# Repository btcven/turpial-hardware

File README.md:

# Turpial Hardware

Source files for Turpial hardware, designed using KiCAD v5.

## License

Copyright (C) 2021 Locha Mesh Developers

Licensed under the OHL-W-v2 Open Hardware license.

See [LICENSE](./LICENSE) for more information.

## The PCB Stack

According to the recomendations of Texas Instruments the stack will be a 4 layers sandwitch containing:

### Layers, view and dimensions

### Vias, view and dimensions

## Plugins and Tools

### Required

#### RF Tools _KICAD PLUGIN_
    URL: https://github.com/easyw/RF-tools-KiCAD

####  Teardrops
    URL: https://github.com/NilujePerchut/kicad_scripts

### Optionals

#### INTERACTIVE BOM _KICAD PLUGIN_
    Description: Generate an interactive html Bill Of Materials (BOM)
    URL: https://github.com/openscopeproject/InteractiveHtmlBom
    
#### GRAPHICAL SYMBOL GENERATOR (KiSymGen) _KICAD PLUGIN_
    Description: KiSymGen is a graphical symbol generator which makes this process visual and less painful.
    URL: https://github.com/pixellon/imgui
    
#### library.io _ONLINE_TOOL_
    Description: Instantly generate PCB packages by entering a few dimensions from a data sheet.
    URL: https://library.io/

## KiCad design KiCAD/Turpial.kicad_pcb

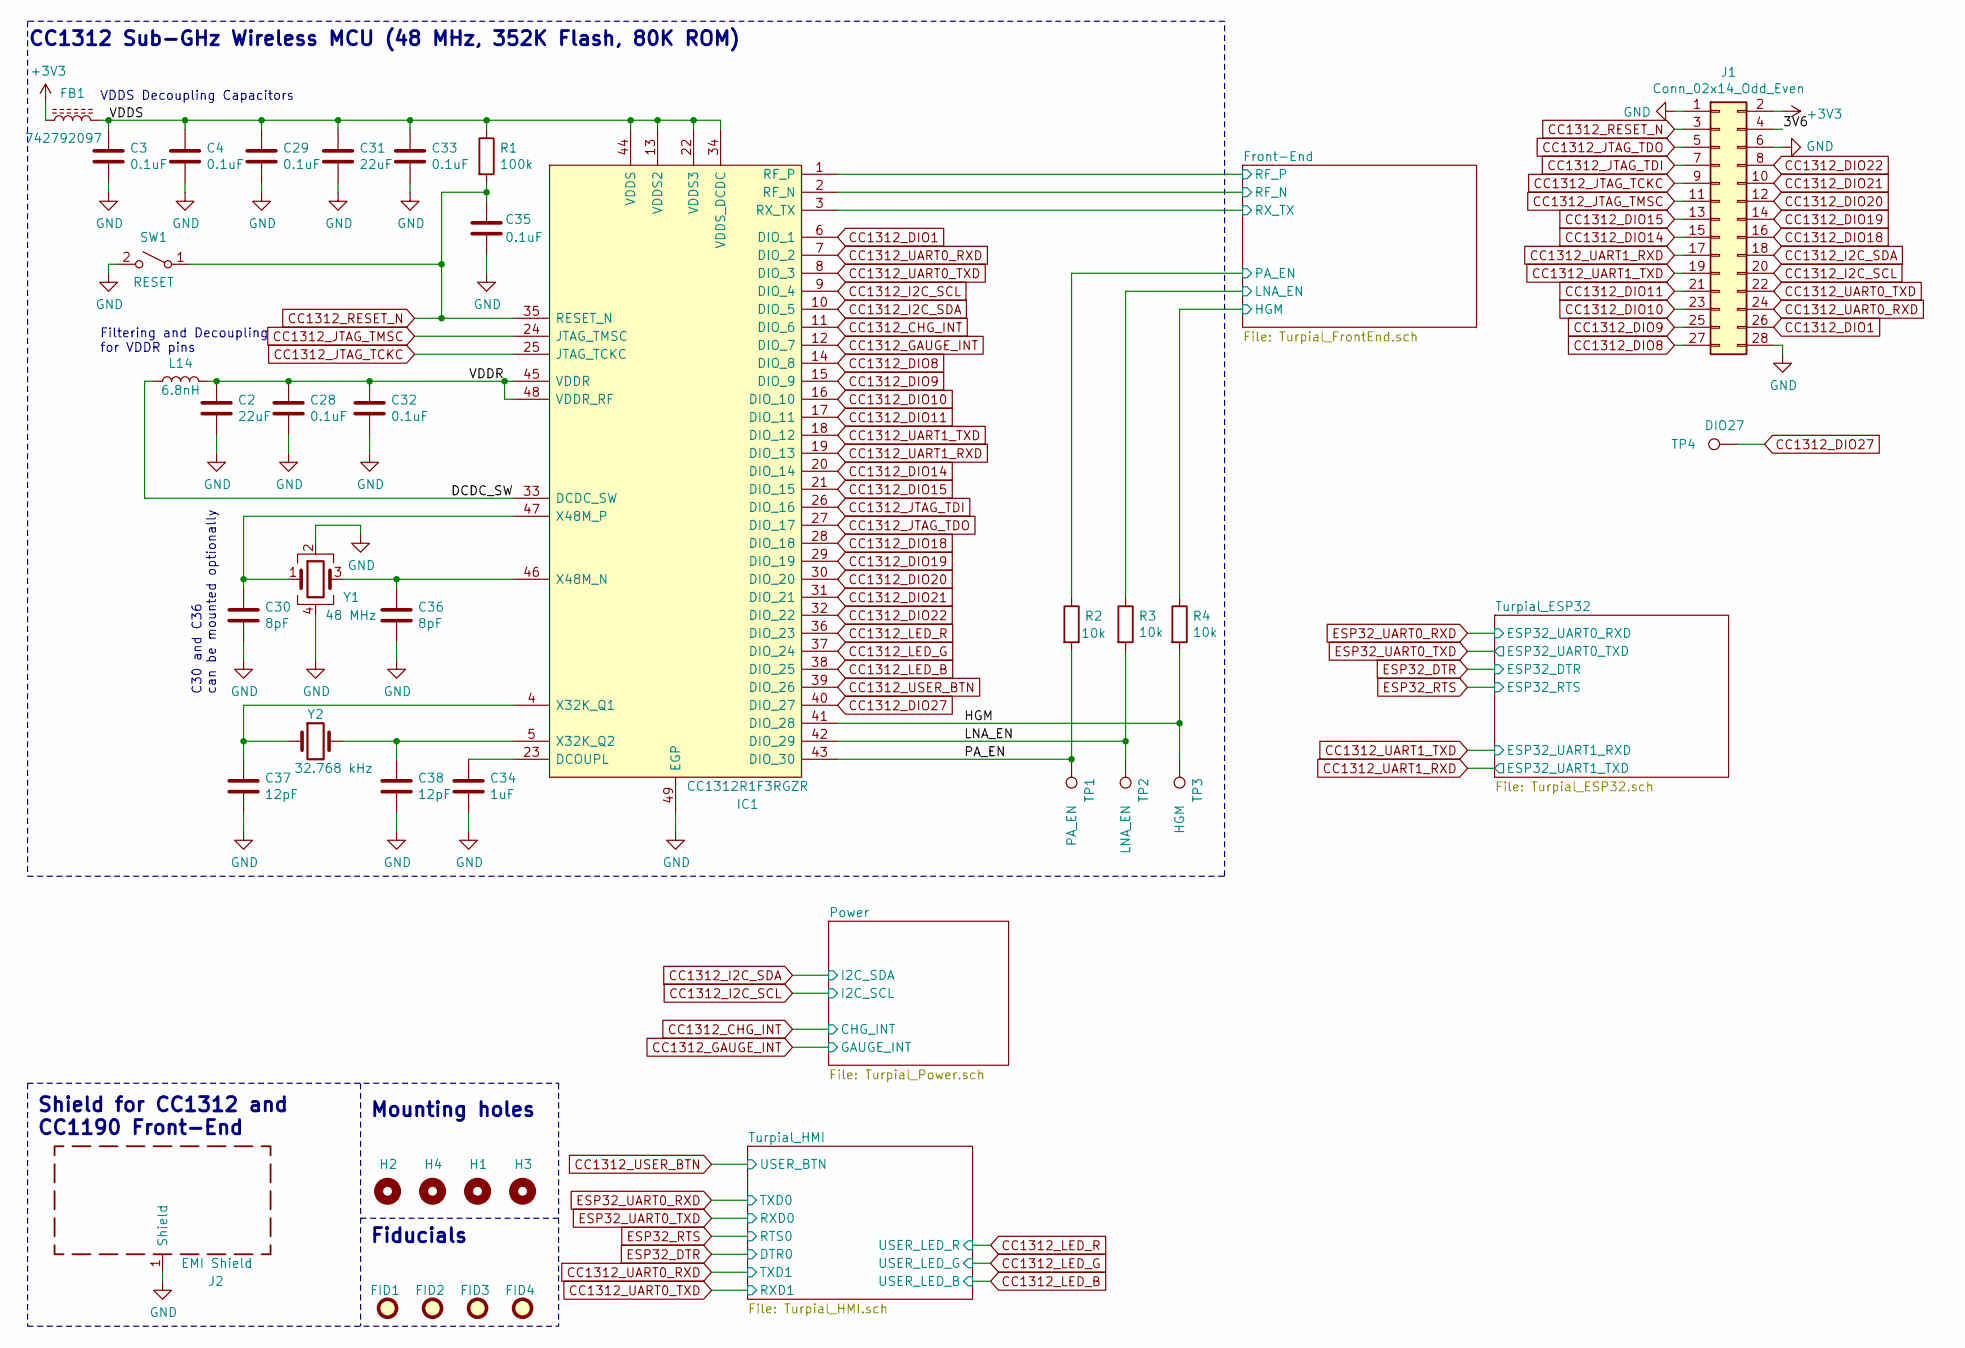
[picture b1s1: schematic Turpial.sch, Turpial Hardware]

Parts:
C2, C31: 22uF; C_0805_2012Metric; Manufacturer_Part_Number GRM21BR61E226ME44L; Mouser Part Number 81-GRM21BR61E226ME4L
C3, C4, C28, C29, C32, C33, C35: 0.1uF; C_0402_1005Metric; Manufacturer_Part_Number GRM155R61H104KE19D; Mouser Part Number 81-GRM155R61H104KE9D
C30, C36: 8pF; C_0402_1005Metric; Manufacturer_Part_Number GRM0225C1E8R0WA03L; Mouser Part Number 81-GRM0225C1E8R0WA3L
C34: 1uF; C_0402_1005Metric; Manufacturer_Part_Number GRM155R61E105KA12D; Mouser Part Number 81-GRM155R61E105KA2D
C37, C38: 12pF; C_0402_1005Metric; Manufacturer_Part_Number GJM1555C1H120JB01D; Mouser Part Number 81-GJM1555C1H120JB1D
FB1: 742792097; L_0805_2012Metric; Manufacturer_Part_Number 742792097; Mouser Part Number 710-742792097
FID1, FID2, FID3, FID4: Fiducial; Fiducial_1mm_Mask2mm
H1, H2, H3, H4: MountingHole; MountingHole_2.5mm_Pad_Via
IC1: CC1312R1F3RGZR; Texas_S-PVQFN-N48_EP5.15x5.15mm_ThermalVias; Manufacturer_Part_Number CC1312R1F3RGZR; Mouser Part Number 595-CC1312R1F3RGZR
J1: Conn_02x14_Odd_Even; PinHeader_2x14_P2.54mm_Vertical_SMD; Manufacturer_Part_Number 15-91-2140; Mouser Part Number 538-15-91-2140
J2: EMI Shield; SMS-461-F; Manufacturer_Part_Number SMS-461F; Mouser Part Number 861-SMS-461F
L14: 6.8nH; L_0805_2012Metric; Manufacturer_Part_Number MLZ2012N6R8LT000; Mouser Part Number 810-MLZ2012N6R8LT000
R1: 100k; R_0402_1005Metric; Manufacturer_Part_Number RC0402FR-7D100KL; Mouser Part Number 603-RC0402FR-7D100KL
R2, R3, R4: 10k; R_0402_1005Metric; Manufacturer_Part_Number RC0402FR-0710KL; Mouser Part Number 603-RC0402FR-0710KL
SW1: RESET; WS-TASU-Series
TP1: PA_EN; TestPoint_Pad_D1.0mm
TP2: LNA_EN; TestPoint_Pad_D1.0mm
TP3: HGM; TestPoint_Pad_D1.0mm
TP4: DIO27; TestPoint_Pad_D1.0mm
Y1: 48 MHz; Crystal_SMD_2016-4Pin_2.0x1.6mm; Manufacturer_Part_Number NX2016SA-48M-EXS00A-CS08718; Mouser Part Number 344-NX2016SA48S08718
Y2: 32.768 kHz; Crystal_SMD_3215-2Pin_3.2x1.5mm; Manufacturer_Part_Number FC-135 32.7680KA-A3; Mouser Part Number 732-FC135-32.76KAA3

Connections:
+3V3: FB1.1, J1.2; also elsewhere on the board
/3V6: J1.4
/DCDC_SW: IC1.33 (DCDC_SW), L14.1
/Front-End/HGM: R4.1; also elsewhere on the board
/Front-End/LNA_EN: R3.1; also elsewhere on the board
/Front-End/PA_EN: R2.1; also elsewhere on the board
/Front-End/RF_N: IC1.2 (RF_N); also elsewhere on the board
/Front-End/RF_P: IC1.1 (RF_P); also elsewhere on the board
/Front-End/RX_TX: IC1.3 (RX_TX); also elsewhere on the board
/HGM: IC1.41 (DIO_28), R4.2, TP3.1
/LNA_EN: IC1.42 (DIO_29), R3.2, TP2.1
/PA_EN: IC1.43 (DIO_30), R2.2, TP1.1
/VDDR: C2.1, C28.1, C32.1, IC1.45 (VDDR), IC1.48 (VDDR_RF), L14.2
/VDDS: C3.1, C4.1, C29.1, C31.1, C33.1, FB1.2, IC1.13 (VDDS2), IC1.22 (VDDS3), IC1.34 (VDDS_DCDC), IC1.44 (VDDS), R1.1
CC1312_CHG_INT: IC1.11 (DIO_6); also elsewhere on the board
CC1312_DIO1: IC1.6 (DIO_1), J1.26
CC1312_DIO8: IC1.14 (DIO_8), J1.27
CC1312_DIO9: IC1.15 (DIO_9), J1.25
CC1312_DIO10: IC1.16 (DIO_10), J1.23
CC1312_DIO11: IC1.17 (DIO_11), J1.21
CC1312_DIO14: IC1.20 (DIO_14), J1.15
CC1312_DIO15: IC1.21 (DIO_15), J1.13
CC1312_DIO18: IC1.28 (DIO_18), J1.16
CC1312_DIO19: IC1.29 (DIO_19), J1.14
CC1312_DIO20: IC1.30 (DIO_20), J1.12
CC1312_DIO21: IC1.31 (DIO_21), J1.10
CC1312_DIO22: IC1.32 (DIO_22), J1.8
CC1312_DIO27: IC1.40 (DIO_27), TP4.1
CC1312_GAUGE_INT: IC1.12 (DIO_7); also elsewhere on the board
CC1312_I2C_SCL: IC1.9 (DIO_4), J1.20; also elsewhere on the board
CC1312_I2C_SDA: IC1.10 (DIO_5), J1.18; also elsewhere on the board
CC1312_JTAG_TCKC: IC1.25 (JTAG_TCKC), J1.9
CC1312_JTAG_TDI: IC1.26 (DIO_16), J1.7
CC1312_JTAG_TDO: IC1.27 (DIO_17), J1.5
CC1312_JTAG_TMSC: IC1.24 (JTAG_TMSC), J1.11
CC1312_LED_B: IC1.38 (DIO_25); also elsewhere on the board
CC1312_LED_G: IC1.37 (DIO_24); also elsewhere on the board
CC1312_LED_R: IC1.36 (DIO_23); also elsewhere on the board
CC1312_RESET_N: C35.1, IC1.35 (RESET_N), J1.3, R1.2, SW1.1 (A)
CC1312_UART0_RXD: IC1.7 (DIO_2), J1.24; also elsewhere on the board
CC1312_UART0_TXD: IC1.8 (DIO_3), J1.22; also elsewhere on the board
CC1312_UART1_RXD: IC1.19 (DIO_13), J1.17; also elsewhere on the board
CC1312_UART1_TXD: IC1.18 (DIO_12), J1.19; also elsewhere on the board
CC1312_USER_BTN: IC1.39 (DIO_26); also elsewhere on the board
GND: C2.2, C3.2, C4.2, C28.2, C29.2, C30.2, C31.2, C32.2, C33.2, C34.2, C35.2, C36.2, C37.2, C38.2, IC1.49 (EGP), J1.1, J1.6, J1.28, J2.1, SW1.2 (B), Y1.2, Y1.4; also elsewhere on the board
unnamed: C30.1, IC1.47 (X48M_P), Y1.1
unnamed: C34.1, IC1.23 (DCOUPL)
unnamed: C36.1, IC1.46 (X48M_N), Y1.3
unnamed: C37.1, IC1.4 (X32K_Q1), Y2.1
unnamed: C38.1, IC1.5 (X32K_Q2), Y2.2

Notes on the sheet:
VDDS Decoupling Capacitors
Filtering and Decoupling for VDDR pins
C30 and C36 can be mounted optionally
CC1312 Sub-GHz Wireless MCU (48 MHz, 352K Flash, 80K ROM)
Shield for CC1312 and CC1190 Front-End
Fiducials
Mounting holes

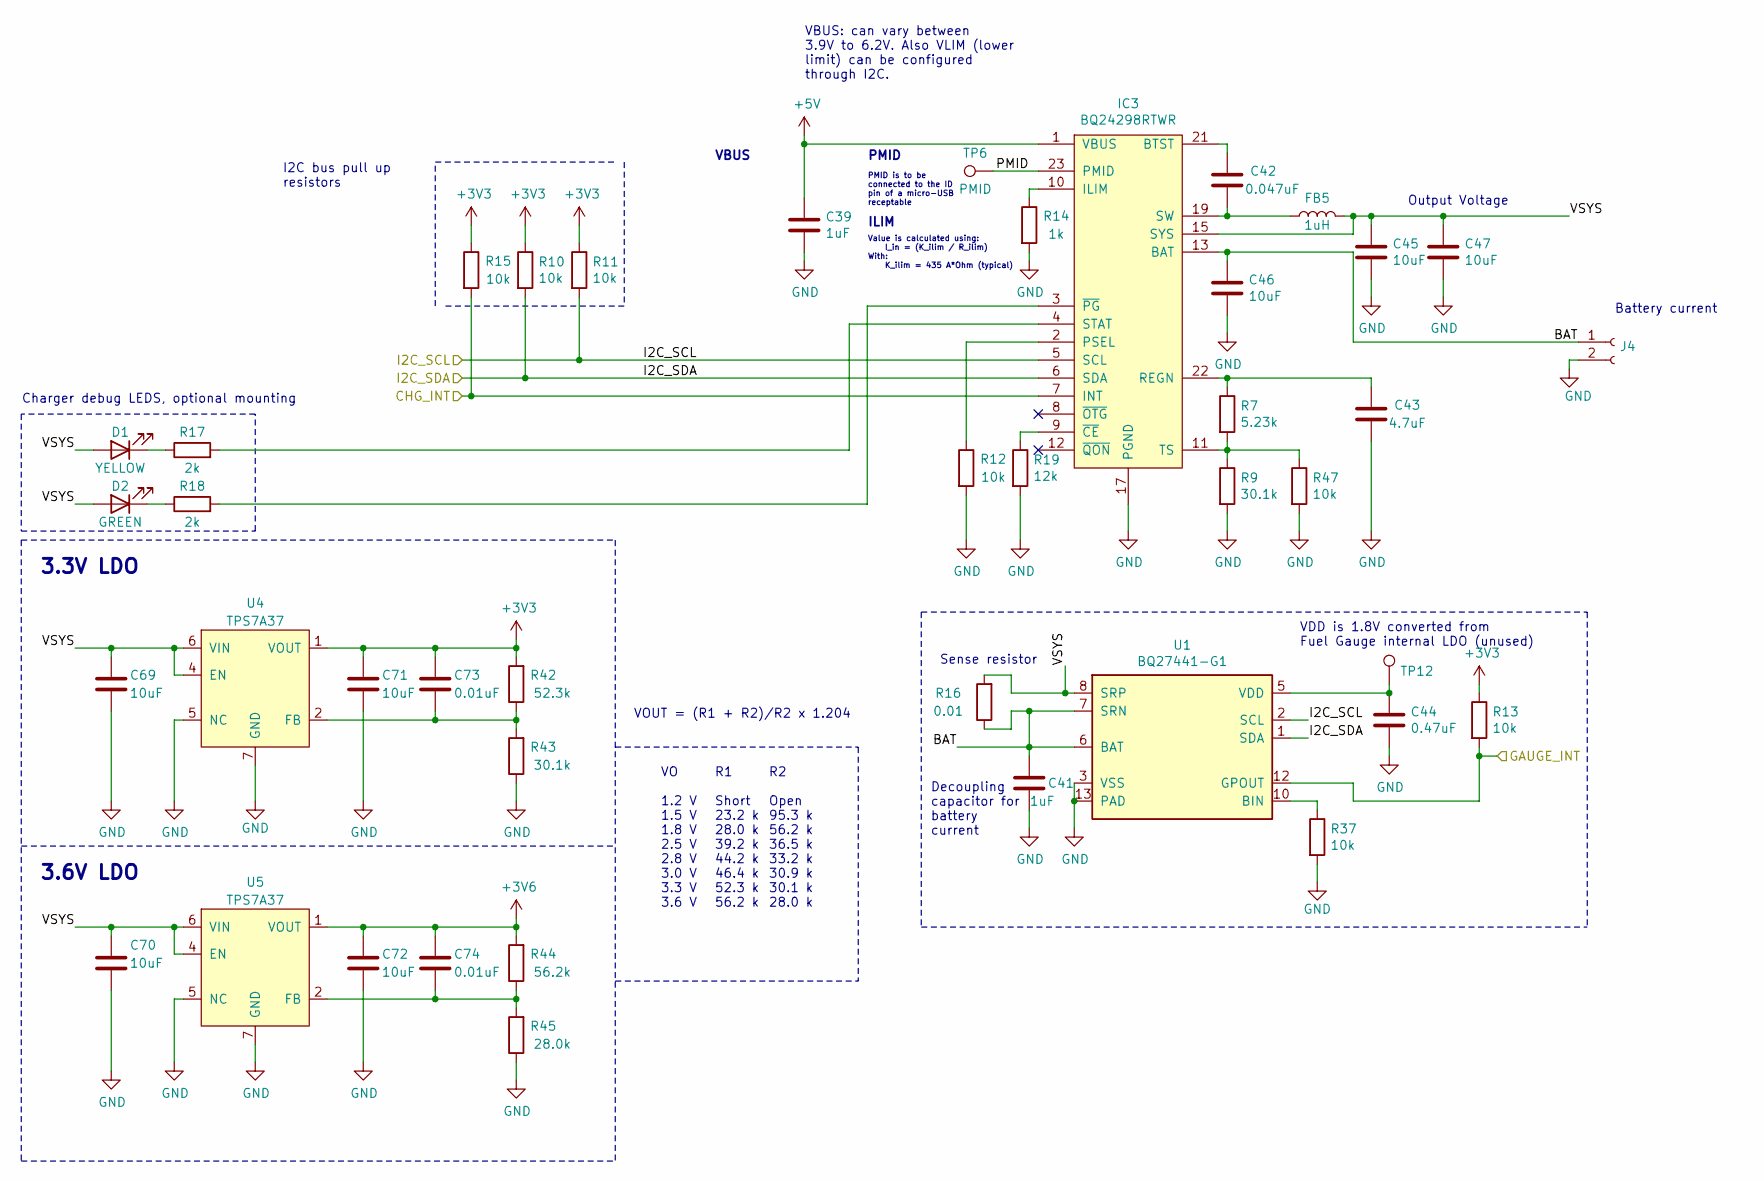
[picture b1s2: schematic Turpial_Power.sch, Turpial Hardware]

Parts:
C39, C41: 1uF; C_0402_1005Metric; Manufacturer_Part_Number GRM155R61E105KA12D; Mouser Part Number 81-GRM155R61E105KA2D
C42: 0.047uF; C_0402_1005Metric; Manufacturer_Part_Number GRM155R71H473KE14D; Mouser Part Number 81-GRM155R71H473KE4D
C43: 4.7uF; C_0402_1005Metric; Manufacturer_Part_Number GRM155R61A475MEAAD; Mouser Part Number 81-GRM155R61A475MEAD
C44: 0.47uF; C_0402_1005Metric; Manufacturer_Part_Number GRM155R71A474KE01D; Mouser Part Number 81-GRM155R71A474KE1D
C45, C46, C47, C69, C70, C71, C72: 10uF; C_0603_1608Metric; Manufacturer_Part_Number GRM188R61E106MA73J; Mouser Part Number 81-GRM188R61E106MA3J
C73, C74: 0.01uF; C_0603_1608Metric; Manufacturer_Part_Number GRM188R72A103KA01D; Mouser Part Number 81-GRM188R72A103KA1D
D1: YELLOW; LED_0603_1608Metric; Manufacturer_Part_Number LTST-C191KRKT; Mouser Part Number 859-LTST-C191KRKT
D2: GREEN; LED_0603_1608Metric; Manufacturer_Part_Number LTST-C191KGKT; Mouser Part Number 859-LTST-C191KGKT
FB5: 1uH; L_0805_2012Metric; Manufacturer_Part_Number DFE201210S-1R0M=P2; Mouser Part Number 81-DFE201210S-1R0MP2
IC3: BQ24298RTWR; Texas_S-PWQFN-N24_EP2.7x2.7mm_ThermalVias; Manufacturer_Part_Number BQ24298RTWR; Mouser Part Number 595-BQ24298RTWR
J4: Conn_01x02_Female; PinHeader_1x02_P2.54mm_Vertical
R7: 5.23k; R_0402_1005Metric; Manufacturer_Part_Number RC0402FR-075K23L; Mouser Part Number 603-RC0402FR-075K23L
R9, R43: 30.1k; R_0603_1608Metric; Manufacturer_Part_Number RC0603FR-0730K1L; Mouser Part Number 603-RC0603FR-0730K1L
R10, R11, R12, R13, R15, R37, R47: 10k; R_0402_1005Metric; Manufacturer_Part_Number RC0402FR-0710KL; Mouser Part Number 603-RC0402FR-0710KL
R14: 1k; R_0603_1608Metric; Manufacturer_Part_Number RC0603FR-071KL; Mouser Part Number 603-RC0603FR-071KL
R16: 0.01; R_0603_1608Metric; Manufacturer_Part_Number MFC0603-R01FT5; Mouser Part Number 756-MFC0603-R01FT5
R17, R18: 2k; R_0402_1005Metric; Manufacturer_Part_Number RC0402FR-072KL; Mouser Part Number 603-RC0402FR-072KL
R19: 12k; R_0402_1005Metric; Manufacturer_Part_Number RC0402FR-0712KL; Mouser Part Number 603-RC0402FR-0712KL
R42: 52.3k; R_0603_1608Metric; Manufacturer_Part_Number RC0603FR-0752K3L; Mouser Part Number 603-RC0603FR-0752K3L
R44: 56.2k; R_0603_1608Metric; Manufacturer_Part_Number RC0603FR-0756K2L; Mouser Part Number 603-RC0603FR-0756K2L
R45: 28.0k; R_0603_1608Metric; Manufacturer_Part_Number RC0603FR-0728KL; Mouser Part Number 603-RC0603FR-0728KL
TP6: PMID; TestPoint_Pad_D1.0mm
TP12: TestPoint; TestPoint_Pad_D1.0mm
U1: BQ27441-G1; Texas_S-PDSO-N12; Manufacturer_Part_Number BQ27441DRZT-G1A; Mouser Part Number 595-BQ27441DRZT-G1A
U4, U5: TPS7A37; Manufacturer_Part_Number TPS7A3701DRVR; Mouser Part Number 595-TPS7A3701DRVR

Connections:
+3V3: C71.1, C73.1, R10.1, R11.1, R13.1, R15.1, R42.2, U4.1 (VOUT); also elsewhere on the board
+3V6: C72.1, C74.1, R44.2, U5.1 (VOUT); also elsewhere on the board
+5V: C39.1, IC3.1 (VBUS), IC3.24 (VBUS); also elsewhere on the board
/Power/BAT: C41.1, C46.2, IC3.13 (BAT), IC3.14 (BAT), J4.1, R16.1, U1.6 (BAT), U1.7 (SRN)
/Power/PMID: IC3.23 (PMID), TP6.1
/Power/VSYS: C45.1, C47.1, C69.1, C70.1, D1.2 (A), D2.2 (A), FB5.2, IC3.15 (SYS), IC3.16 (SYS), R16.2, U1.8 (SRP), U4.4 (EN), U4.6 (VIN), U5.4 (EN), U5.6 (VIN)
CC1312_CHG_INT: IC3.7 (INT), R15.2; also elsewhere on the board
CC1312_GAUGE_INT: R13.2, U1.12 (GPOUT); also elsewhere on the board
CC1312_I2C_SCL: IC3.5 (SCL), R11.2, U1.2 (SCL); also elsewhere on the board
CC1312_I2C_SDA: IC3.6 (SDA), R10.2, U1.1 (SDA); also elsewhere on the board
GND: C39.2, C41.2, C43.2, C44.2, C45.2, C46.1, C47.2, C69.2, C70.2, C71.2, C72.2, IC3.17 (PGND), IC3.18 (PGND), IC3.25 (GND), J4.2, R9.2, R12.2, R14.2, R19.2, R37.2, R43.1, R45.1, R47.2, U1.3 (VSS), U1.13 (PAD), U4.3 (GND), U4.5 (NC), U4.7 (GND), U5.3 (GND), U5.5 (NC), U5.7 (GND); also elsewhere on the board
unnamed: C42.1, FB5.1, IC3.19 (SW), IC3.20 (SW)
unnamed: C42.2, IC3.21 (BTST)
unnamed: C43.1, IC3.22 (REGN), R7.1
unnamed: C44.1, TP12.1, U1.5 (VDD)
unnamed: C73.2, R42.1, R43.2, U4.2 (FB)
unnamed: C74.2, R44.1, R45.2, U5.2 (FB)
unnamed: D1.1 (K), R17.1
unnamed: D2.1 (K), R18.1
unnamed: IC3.2 (PSEL), R12.1
unnamed: IC3.3 (~PG), R18.2
unnamed: IC3.4 (STAT), R17.2
unnamed: IC3.9 (~CE), R19.1
unnamed: IC3.10 (ILIM), R14.1
unnamed: IC3.11 (TS), R7.2, R9.1, R47.1
unnamed: R37.1, U1.10 (BIN)

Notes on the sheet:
VBUS: can vary between 3.9V to 6.2V. Also VLIM (lower limit) can be configured through I2C.
ILIM
3.3V LDO
3.6V LDO
VOUT = (R1 + R2)/R2 x 1.204
R1 Short 23.2 k 28.0 k 39.2 k 44.2 k 46.4 k 52.3 k 56.2 k
R2 Open 95.3 k 56.2 k 36.5 k 33.2 k 30.9 k 30.1 k 28.0 k
Charger debug LEDS, optional mounting
VDD is 1.8V converted from Fuel Gauge internal LDO (unused)
Sense resistor
Decoupling capacitor for battery current
I2C bus pull up resistors
Output Voltage
PMID
VO 1.2 V 1.5 V 1.8 V 2.5 V 2.8 V 3.0 V 3.3 V 3.6 V
Battery current
Value is calculated using: I_in = (K_ilim / R_ilim) With: K_ilim = 435 A*Ohm (typical)
VBUS
PMID is to be connected to the ID pin of a micro-USB receptable

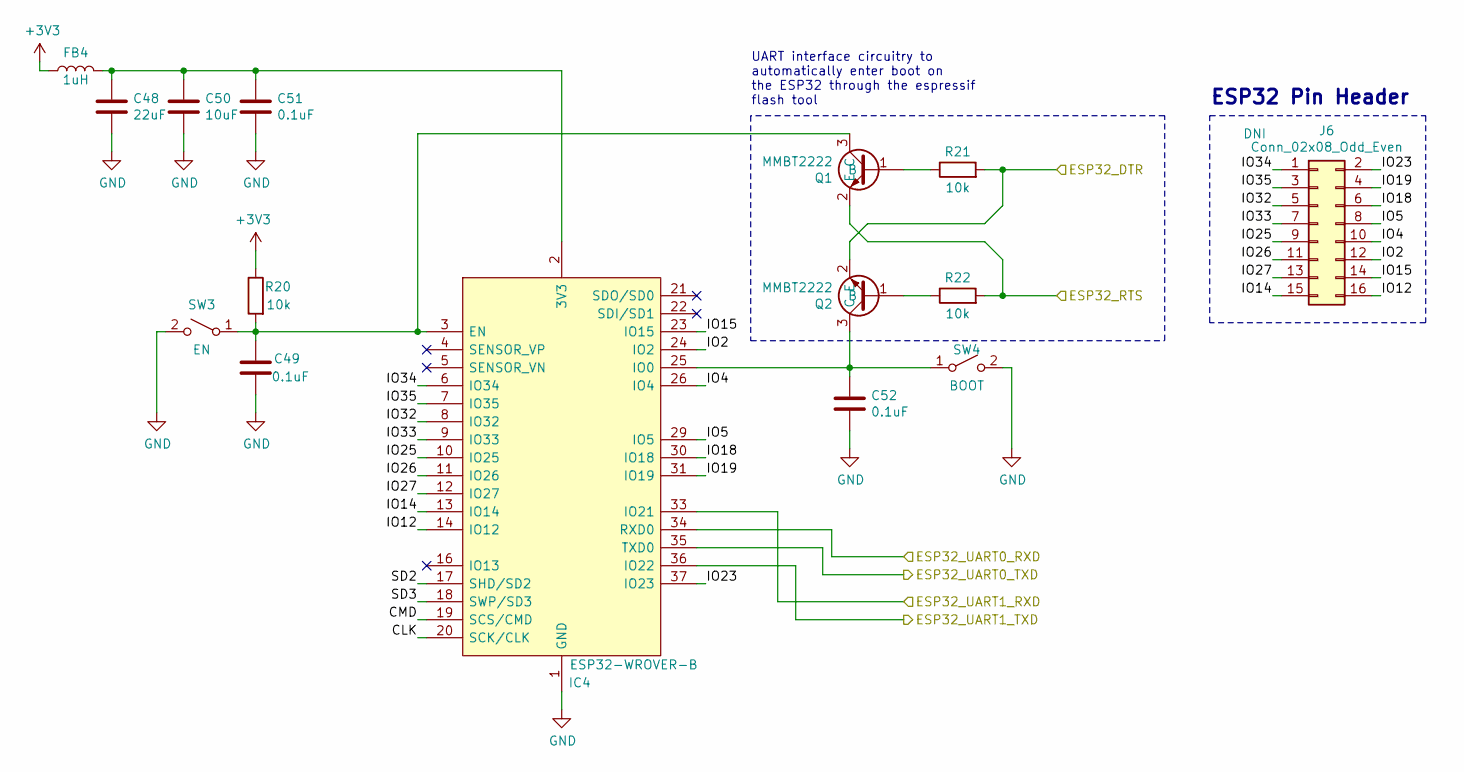
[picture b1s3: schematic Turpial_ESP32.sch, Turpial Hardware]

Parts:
C48: 22uF; C_0805_2012Metric; Manufacturer_Part_Number GRM21BR61E226ME44L; Mouser Part Number 81-GRM21BR61E226ME4L
C49, C51, C52: 0.1uF; C_0402_1005Metric; Manufacturer_Part_Number GRM155R61H104KE19D; Mouser Part Number 81-GRM155R61H104KE9D
C50: 10uF; C_0603_1608Metric; Manufacturer_Part_Number GRM188R61E106MA73J; Mouser Part Number 81-GRM188R61E106MA3J
FB4: 1uH; L_0805_2012Metric; Manufacturer_Part_Number DFE201210S-1R0M=P2; Mouser Part Number 81-DFE201210S-1R0MP2
IC4: ESP32-WROVER-B; Manufacturer_Part_Number ESP32-WROVER-B(M213DH3264PH3Q0); Mouser Part Number 356-ESP32-WROVER-B
J6: Conn_02x08_Odd_Even; PinHeader_2x08_P2.54mm_Vertical_SMD; Manufacturer_Part_Number 71308-5408; Mouser Part Number 538-71308-5408
Q1, Q2: MMBT2222; SOT-23; Manufacturer_Part_Number MMBT2222ALT1G; Mouser Part Number 863-MMBT2222ALT1G
R20, R21, R22: 10k; R_0402_1005Metric; Manufacturer_Part_Number RC0402FR-0710KL; Mouser Part Number 603-RC0402FR-0710KL
SW3: EN; WS-TASU-Series
SW4: BOOT; WS-TASU-Series

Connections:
+3V3: FB4.1, R20.1; also elsewhere on the board
/Turpial_ESP32/CLK: IC4.20 (SCK/CLK)
/Turpial_ESP32/CMD: IC4.19 (SCS/CMD)
/Turpial_ESP32/IO2: IC4.24 (IO2), J6.12
/Turpial_ESP32/IO4: IC4.26 (IO4), J6.10
/Turpial_ESP32/IO5: IC4.29 (IO5), J6.8
/Turpial_ESP32/IO12: IC4.14 (IO12), J6.16
/Turpial_ESP32/IO14: IC4.13 (IO14), J6.15
/Turpial_ESP32/IO15: IC4.23 (IO15), J6.14
/Turpial_ESP32/IO18: IC4.30 (IO18), J6.6
/Turpial_ESP32/IO19: IC4.31 (IO19), J6.4
/Turpial_ESP32/IO23: IC4.37 (IO23), J6.2
/Turpial_ESP32/IO25: IC4.10 (IO25), J6.9
/Turpial_ESP32/IO26: IC4.11 (IO26), J6.11
/Turpial_ESP32/IO27: IC4.12 (IO27), J6.13
/Turpial_ESP32/IO32: IC4.8 (IO32), J6.5
/Turpial_ESP32/IO33: IC4.9 (IO33), J6.7
/Turpial_ESP32/IO34: IC4.6 (IO34), J6.1
/Turpial_ESP32/IO35: IC4.7 (IO35), J6.3
/Turpial_ESP32/SD2: IC4.17 (SHD/SD2)
/Turpial_ESP32/SD3: IC4.18 (SWP/SD3)
CC1312_UART1_RXD: IC4.36 (IO22); also elsewhere on the board
CC1312_UART1_TXD: IC4.33 (IO21); also elsewhere on the board
ESP32_DTR: Q2.2 (E), R21.2; also elsewhere on the board
ESP32_RTS: Q1.2 (E), R22.2; also elsewhere on the board
ESP32_UART0_RXD: IC4.34 (RXD0); also elsewhere on the board
ESP32_UART0_TXD: IC4.35 (TXD0); also elsewhere on the board
GND: C48.2, C49.2, C50.2, C51.2, C52.2, IC4.1 (GND), IC4.15 (GND), IC4.38 (GND), IC4.39 (GND), SW3.2 (B), SW4.2 (B); also elsewhere on the board
unnamed: C48.1, C50.1, C51.1, FB4.2, IC4.2 (3V3)
unnamed: C49.1, IC4.3 (EN), Q1.3 (C), R20.2, SW3.1 (A)
unnamed: C52.1, IC4.25 (IO0), Q2.3 (C), SW4.1 (A)
unnamed: Q1.1 (B), R21.1
unnamed: Q2.1 (B), R22.1

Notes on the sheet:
UART interface circuitry to automatically enter boot on the ESP32 through the espressif flash tool
ESP32 Pin Header

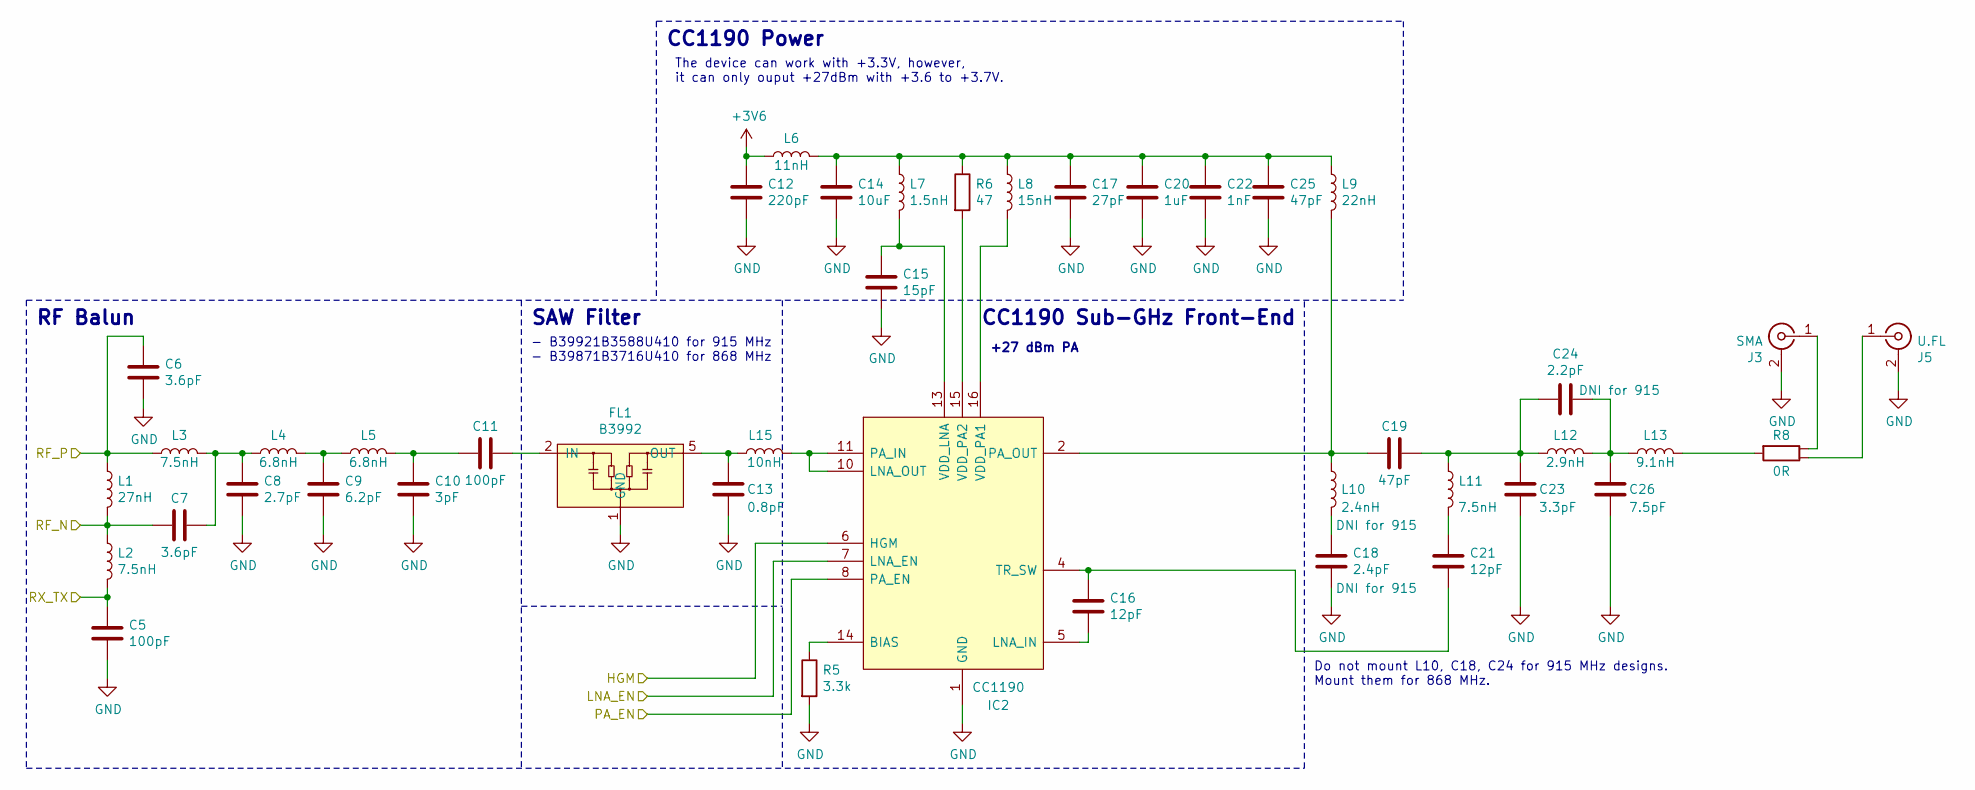
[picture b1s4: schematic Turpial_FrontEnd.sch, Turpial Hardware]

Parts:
C5, C11: 100pF; C_0402_1005Metric; Manufacturer_Part_Number GCM1555C1H101JA16D; Mouser Part Number 81-GCM1555C1H101JA6D
C6, C7: 3.6pF; C_0402_1005Metric; Manufacturer_Part_Number GJM1555C1H3R6CB01D; Mouser Part Number 81-GJM1555C1H3R6CB1D
C8: 2.7pF; C_0402_1005Metric; Manufacturer_Part_Number GJM1555C1H2R7CB01D; Mouser Part Number 81-GJM1555C1H2R7CB1D
C9: 6.2pF; C_0402_1005Metric; Manufacturer_Part_Number GJM1555C1H6R2CB01D; Mouser Part Number 81-GJM1555C1H6R2CB01
C10: 3pF; C_0402_1005Metric; Manufacturer_Part_Number GJM1555C1H3R0CB01D; Mouser Part Number 81-GJM1555C1H3R0CB1D
C12: 220pF; C_0402_1005Metric; Manufacturer_Part_Number GCM1555C1H221JA16D; Mouser Part Number 81-GCM1555C1H221J16D
C13: 0.8pF; C_0402_1005Metric; Manufacturer_Part_Number GJM1555C1HR80DB01J; Mouser Part Number 81-GJM1555C1HR80DB1J
C14: 10uF; C_0603_1608Metric; Manufacturer_Part_Number GRM188R61E106MA73J; Mouser Part Number 81-GRM188R61E106MA3J
C15: 15pF; C_0402_1005Metric; Manufacturer_Part_Number GJM1555C1H150JB01J; Mouser Part Number 81-GJM1555C1H150JB1J
C16, C21: 12pF; C_0402_1005Metric; Manufacturer_Part_Number GJM1555C1H120JB01D; Mouser Part Number 81-GJM1555C1H120JB1D
C17: 27pF; C_0402_1005Metric; Manufacturer_Part_Number GJM1555C1H270JB01D; Mouser Part Number 81-GJM1555C1H270JB1D
C18: 2.4pF; C_0402_1005Metric; Manufacturer_Part_Number GJM1555C1H2R4CB01D; Mouser Part Number 81-GJM1555C1H2R4CB1D
C19, C25: 47pF; C_0402_1005Metric; Manufacturer_Part_Number GJM1555C1H470JB01J; Mouser Part Number 81-GJM1555C1H470JB1J
C20: 1uF; C_0402_1005Metric; Manufacturer_Part_Number GRM155R61E105KA12D; Mouser Part Number 81-GRM155R61E105KA2D
C22: 1nF; C_0402_1005Metric; Manufacturer_Part_Number GCM155R71H102KA37D; Mouser Part Number 81-GCM155R71H102KA7D
C23: 3.3pF; C_0402_1005Metric; Manufacturer_Part_Number GJM1555C1H3R3CB01D; Mouser Part Number 81-GJM1555C1H3R3CB1D
C24: 2.2pF; C_0402_1005Metric; Manufacturer_Part_Number GJM1555C1H2R2CB01D; Mouser Part Number 81-GJM1555C1H2R2CB1D
C26: 7.5pF; C_0402_1005Metric; Manufacturer_Part_Number GJM1555C1H7R5CB01D; Mouser Part Number 81-GJM1555C1H7R5CB01
FL1: B3992; FIL_B39921B3588U410; Manufacturer_Part_Number B39921B3588U410; Mouser Part Number 871-B39921B3588U410
IC2: CC1190; Texas_S-PVQFN-N16_EP2.7x2.7mm_ThermalVias; Manufacturer_Part_Number CC1190RGVR; Mouser Part Number 595-CC1190RGVR
J3: SMA; SMA_EDGEMOUNT
J5: U.FL; U.FL_Linx_CONUFL001-SMD-T; Manufacturer_Part_Number CONUFL001-SMD-T; Mouser Part Number 712-CONUFL001-SMD-T
L1: 27nH; L_0402_1005Metric; Manufacturer_Part_Number LQG15HS27NJ02D; Mouser Part Number 81-LQG15HS27NJ02D
L2, L3, L11: 7.5nH; L_0402_1005Metric; Manufacturer_Part_Number LQW15AN7N5G00D; Mouser Part Number 81-LQW15AN7N5G00D
L4, L5: 6.8nH; L_0402_1005Metric; Manufacturer_Part_Number LQG15HS6N8J02D; Mouser Part Number 81-LQG15HS6N8J02D
L6: 11nH; L_0402_1005Metric; Manufacturer_Part_Number LQW15AN11NJ00D; Mouser Part Number 81-LQW15AN11NJ00D
L7: 1.5nH; L_0402_1005Metric; Manufacturer_Part_Number LQG15HS1N5S02D; Mouser Part Number 81-LQG15HS1N5S02D
L8: 15nH; L_0402_1005Metric; Manufacturer_Part_Number LQW15AN15NJ00D; Mouser Part Number 81-LQW15AN15NJ00D
L9: 22nH; L_0603_1608Metric; Manufacturer_Part_Number LQW18AN22NJ10D; Mouser Part Number 81-LQW18AN22NJ10D
L10: 2.4nH; L_0402_1005Metric
L12: 2.9nH; L_0402_1005Metric; Manufacturer_Part_Number LQW15AN2N9C00D; Mouser Part Number 81-LQW15AN2N9C00D
L13: 9.1nH; L_0402_1005Metric; Manufacturer_Part_Number LQW15AN9N1G00D; Mouser Part Number 81-LQW15AN9N1G00D
L15: 10nH; L_0402_1005Metric; Manufacturer_Part_Number LQW15AN10NJ00D; Mouser Part Number 81-LQW15AN10NJ00D
R5: 3.3k; R_0402_1005Metric; Manufacturer_Part_Number RC0402FR-7D3K3L; Mouser Part Number 603-RC0402FR-7D3K3L
R6: 47; R_0402_1005Metric; Manufacturer_Part_Number RC0402FR-0747RL; Mouser Part Number 603-RC0402FR-0747RL
R8: 0R; YR_0402

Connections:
+3V6: C12.1, L6.1; also elsewhere on the board
/Front-End/HGM: IC2.6 (HGM); also elsewhere on the board
/Front-End/LNA_EN: IC2.7 (LNA_EN); also elsewhere on the board
/Front-End/PA_EN: IC2.8 (PA_EN); also elsewhere on the board
/Front-End/RF_N: C7.2, L1.2, L2.1; also elsewhere on the board
/Front-End/RF_P: C6.2, L1.1, L3.1; also elsewhere on the board
/Front-End/RX_TX: C5.1, L2.2; also elsewhere on the board
GND: C5.2, C6.1, C8.2, C9.2, C10.2, C12.2, C13.2, C14.2, C15.2, C17.2, C18.2, C20.2, C22.2, C23.2, C25.2, C26.2, FL1.1 (GND), FL1.3 (GND), FL1.4 (GND), FL1.6 (GND), IC2.1 (GND), IC2.3 (GND), IC2.9 (GND), IC2.12 (GND), IC2.17 (GND), J3.2 (Ext), J5.2 (Ext), R5.2; also elsewhere on the board
unnamed: C7.1, C8.1, L3.2, L4.1
unnamed: C9.1, L4.2, L5.1
unnamed: C10.1, C11.2, L5.2
unnamed: C11.1, FL1.2 (IN)
unnamed: C13.1, FL1.5 (OUT), L15.1
unnamed: C14.1, C17.1, C20.1, C22.1, C25.1, L6.2, L7.1, L8.1, L9.1, R6.1
unnamed: C15.1, IC2.13 (VDD_LNA), L7.2
unnamed: C16.1, C21.2, IC2.4 (TR_SW)
unnamed: C16.2, IC2.5 (LNA_IN)
unnamed: C18.1, L10.2
unnamed: C19.1, C23.1, C24.2, L11.1, L12.1
unnamed: C19.2, IC2.2 (PA_OUT), L9.2, L10.1
unnamed: C21.1, L11.2
unnamed: C24.1, C26.1, L12.2, L13.1
unnamed: IC2.10 (LNA_OUT), IC2.11 (PA_IN), L15.2
unnamed: IC2.14 (BIAS), R5.1
unnamed: IC2.15 (VDD_PA2), R6.2
unnamed: IC2.16 (VDD_PA1), L8.2
unnamed: J3.1 (In), R8.2
unnamed: J5.1 (In), R8.3
unnamed: L13.2, R8.1

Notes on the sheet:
Do not mount L10, C18, C24 for 915 MHz designs. Mount them for 868 MHz.
RF Balun
SAW Filter
- B39921B3588U410 for 915 MHz - B39871B3716U410 for 868 MHz
CC1190 Sub-GHz Front-End
+27 dBm PA
CC1190 Power
The device can work with +3.3V, however, it can only ouput +27dBm with +3.6 to +3.7V.
